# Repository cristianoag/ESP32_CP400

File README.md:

# The Retro Hacker Clone Series: ESP32 CP400

An open hardware and software project to recreate the spirit of the Prologica CP 400, the Brazilian TRS-80 Color Computer 2 compatible home computer, using a modern ESP32-S3 based design.

This design is part of the Retro Hacker ESP32 Clone Series: a planned collection of ESP32-based recreations of classic Brazilian computers from the 1980s. Each machine in the series focuses on keeping the original character and software culture alive while using practical, buildable modern hardware.

The goal is not to build a museum prop. The goal is to make a usable, hackable CP400-inspired machine: real connectors, real keyboard and joystick paths, VGA output, SD-backed storage, and firmware that can run a CoCo 2 / CP400 style environment on inexpensive contemporary hardware.

## Why CP400?

The Prologica CP 400 was one of the memorable Brazilian home computers of the mid-1980s. Built during Brazil's market-reserve era, it was compatible with the Tandy/Radio Shack TRS-80 Color Computer 2, known as the CoCo 2, but arrived with its own Brazilian industrial design, PAL-M video expectations, local peripherals, translated software, and a very particular place in the local 8-bit scene.

Under the hood, the original CP400 family followed the CoCo architecture closely:

- Motorola MC6809E CPU running around 0.895 MHz
- Motorola MC6847 video display generator
- 16 KB or 64 KB RAM configurations
- Extended Color BASIC in ROM
- Cassette, cartridge, joystick, serial, video, and expansion interfaces
- Optional disk support through the CP450 floppy system

This repository explores that machine from both sides: hardware that gives the emulator a dedicated physical home, and software that recreates the CP400/CoCo experience on an ESP32-S3.

## Heritage

<p align="center">
	
	&nbsp;&nbsp;&nbsp;&nbsp;
	
</p>

The ESP32 CP400 sits between two histories: Prologica's Brazilian CP400 family and the Tandy/Radio Shack CoCo 2 platform that inspired it. The project uses those references as historical anchors while building a new, independent ESP32-based recreation.

## Project Goals

- Preserve the CP400/CoCo 2 experience in a form that can be built, studied, and modified.
- Establish the CP400 entry in the broader ESP32 Clone Series for Retro Hacker.
- Use modern parts where they make sense, especially the ESP32-S3 with PSRAM.
- Provide a KiCad hardware design for a CP400-inspired board and peripheral connectors.
- Run an embedded CoCo 2 style emulator with video, USB input, SD storage, virtual disks, and joystick support.
- Keep the design approachable for retrocomputing builders, hardware hackers, and firmware tinkerers.

## Repository Layout

```text
hardware/esp32_clones/         KiCad project for the generic ESP32 clone hardware
hardware/esp32_clones/libraries Project-local KiCad symbols and footprints
software/esp32_cp400_emulator/ PlatformIO firmware for the ESP32-S3 emulator
case/                          Mechanical/case work area
```

## Hardware

The KiCad project lives in `hardware/esp32_clones` and is named `esp32_clones`.

The local KiCad libraries are organized inside:

```text
hardware/esp32_clones/libraries/symbols
hardware/esp32_clones/libraries/footprints
```

The hardware design currently includes project-local footprints and symbols for the ESP32-S3 module, USB connectors, SD card socket, switches, and other board-level parts. The intent is to give the firmware a board that feels more like a small computer than a loose dev kit on a bench.

## Firmware

The firmware lives in `software/esp32_cp400_emulator` and is built with PlatformIO using the Arduino framework for ESP32-S3.

Current software areas include:

- MC6809 emulator core integration
- CoCo 2 / CP400 video mode handling
- VGA output through the ESP32-S3 VGA library
- USB soft-host input support
- SD/MMC storage access
- Virtual floppy disk image handling
- Emulator menu and firmware updater code
- Joystick and keyboard mapping hooks

The PlatformIO environment is configured for an ESP32-S3 DevKitC-style board with 16 MB flash and 8 MB PSRAM:

```ini
[env:esp32-s3-devkitc-1-Modded]
platform = espressif32@6.11.0
board = esp32-s3-devkitc-1-n16r8
framework = arduino
```

The project intentionally pins the Espressif platform version because newer Arduino/ESP32 combinations may change includes and behavior used by the emulator.

### F12 Firmware Update Package

From `software/esp32_cp400_emulator`, generate a firmware package for the F12 update menu with:

```console
make firmware
```

The command builds the configured PlatformIO environment and creates a versioned package such as `dist/ESP32_CP400-1.11.FLH`. Copy that `.FLH` file to the root of the CP400 microSD card, then select **Firmware update** from the F12 menu.

Set the firmware version with `FW_VERSION` near the top of the Makefile, using one major digit and two minor digits. It is compiled into the F12 menu and used in the package filename. A one-off version can be built without editing the file:

```console
make firmware FW_VERSION=1.11
```

The command names can be overridden when needed, for example:

```console
make firmware PIO=platformio PYTHON=py
```

On Windows, the Makefile automatically detects PlatformIO in `%USERPROFILE%/.platformio/penv/Scripts`. Use `make help` to display the detected command.

Firmware release changes are tracked in `software/esp32_cp400_emulator/docs/log.md`.

## Status

This project is under active development. Expect the hardware, pin mapping, emulator behavior, and documentation to evolve together.

Good entry points:

- Open the KiCad project at `hardware/esp32_clones/esp32_clones.kicad_pro`.
- Open the firmware workspace at `software/esp32_cp400_emulator/esp32_cp400_emulator.code-workspace`.
- Review `software/esp32_cp400_emulator/platformio.ini` before building or uploading.

## ROMs and Original Software

Original CP400, CoCo, Extended Color BASIC, Disk BASIC, cartridge, cassette, and floppy software may still be copyrighted. This repository is for original hardware/firmware work and project files. Bring your own legally obtained ROMs and software images when needed.

## Historical Notes

The CP400 was part of a wider Brazilian TRS-Color ecosystem that included machines such as the Codimex CD-6809, LZ Color 64, Dynacom MX-1600, and Varix VC50. The CP400 became the best-known of the Brazilian CoCo-compatible machines, before the home computer market shifted heavily toward MSX and, later, IBM PC compatibles.

That makes it a particularly interesting target for a modern recreation: it sits at the meeting point of Brazilian microcomputer history, Motorola 6809 elegance, CoCo software culture, and the practical charm of 1980s home computing.

## References and Further Reading

- [Prologica CP-400](https://en.wikipedia.org/wiki/Prol%C3%B3gica_CP-400)
- [CP400](https://pt.wikipedia.org/wiki/CP400)
- [TRS-80 Color Computer](https://en.wikipedia.org/wiki/TRS-80_Color_Computer)
- [Prologica](https://pt.wikipedia.org/wiki/Prol%C3%B3gica)
- [Datassette](https://datassette.org/) for Brazilian retrocomputing manuals, magazines, books, and software preservation material

## License

See `LICENSE.txt` for the repository license. The firmware directory also includes its own `license.txt`; check both before reusing or redistributing project materials.

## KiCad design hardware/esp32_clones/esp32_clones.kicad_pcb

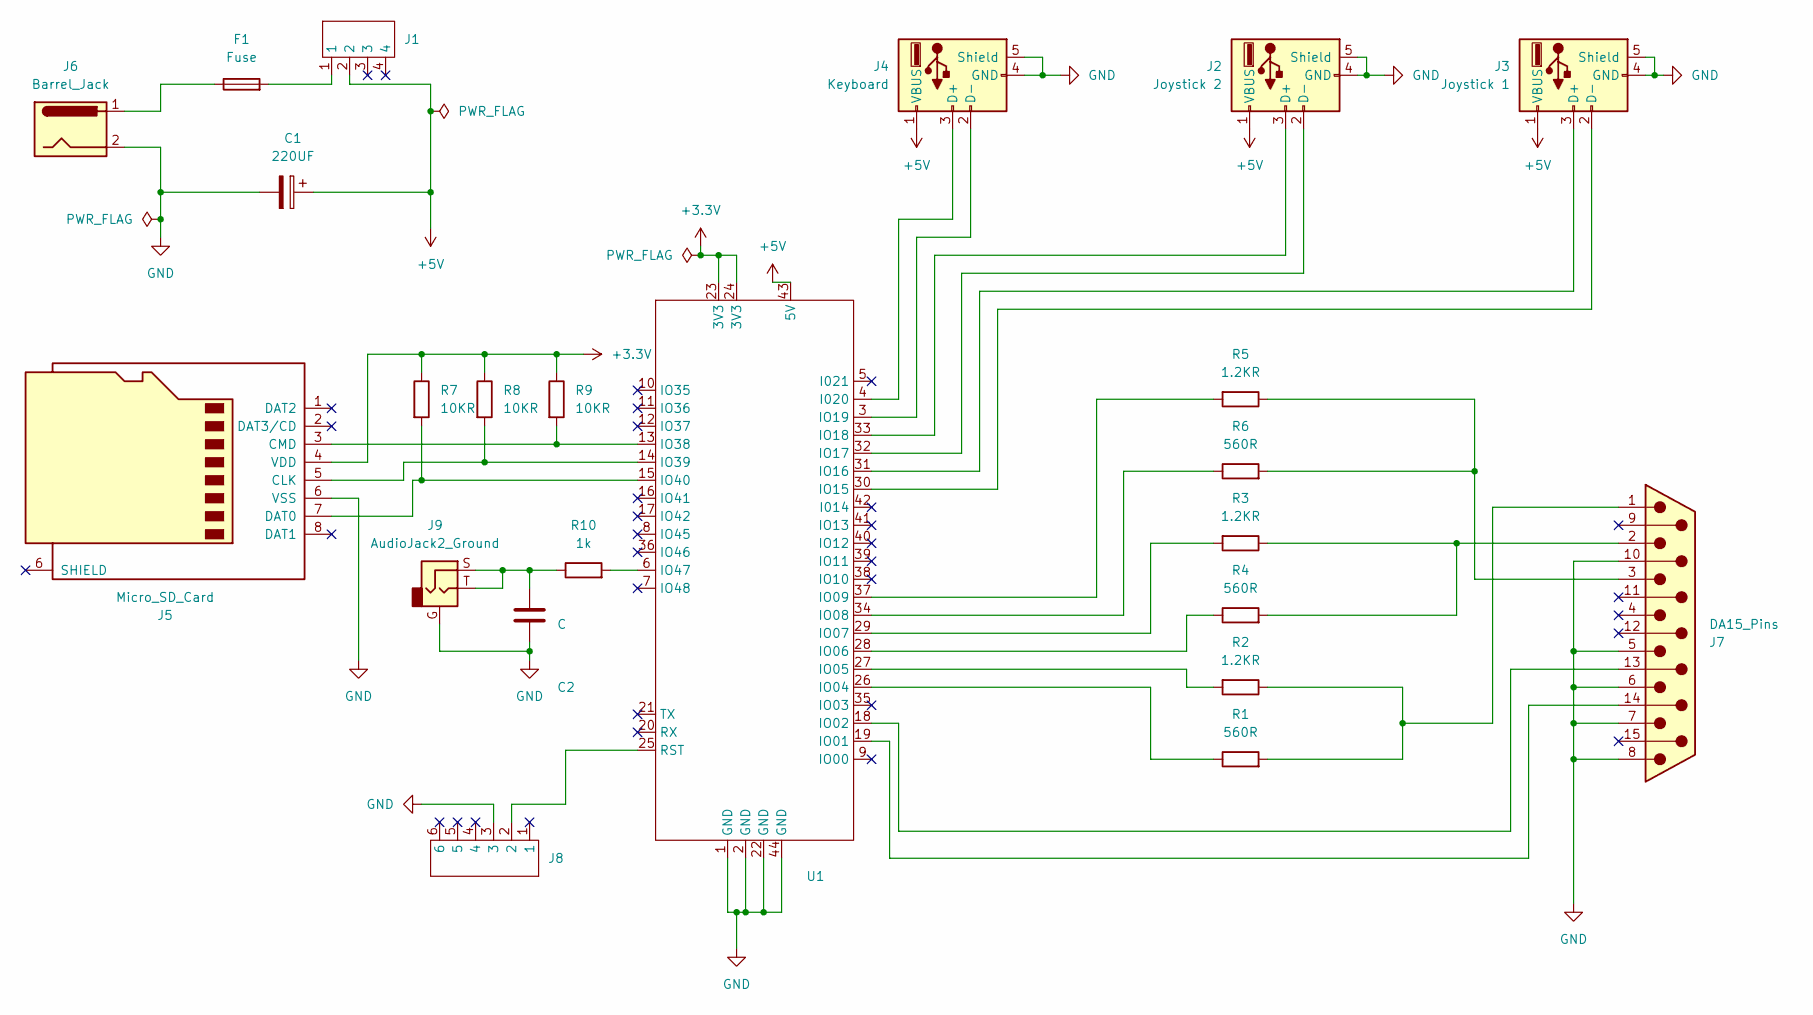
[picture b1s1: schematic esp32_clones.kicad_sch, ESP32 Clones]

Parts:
C1: 220UF; CP_Elec_6.3x3
C2: C; C_0805_2012Metric_Pad1.18x1.45mm_HandSolder
F1: Fuse; Fuse_1210_3225Metric
J1: PS-12E05
J2: Joystick 2; TE_6364372-2
J3: Joystick 1; TE_6364372-2
J4: Keyboard; TE_6364372-2
J5: Micro_SD_Card; Conn_uSDcard
J6: Barrel_Jack; BarrelJack_Horizontal
J7: DA15_Pins; DSUB-15-HD_Socket_Horizontal_P2.29x1.90mm_EdgePinOffset3.03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
J8: PS-22F05
J9: AudioJack2_Ground; PJ-307
R1, R4, R6: 560R; R_0805_2012Metric_Pad1.20x1.40mm_HandSolder
R2, R3, R5: 1.2KR; R_0805_2012Metric_Pad1.20x1.40mm_HandSolder
R7, R8, R9: 10KR; R_0805_2012Metric_Pad1.20x1.40mm_HandSolder
R10: 1k; R_0805_2012Metric_Pad1.20x1.40mm_HandSolder
U1: ESP32-S3-WROOM-1

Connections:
+3.3V: J5.4 (VDD), R7.1, R8.1, R9.1, U1.23 (3V3), U1.24 (3V3)
+5V: C1.1, J1.2, J2.1 (VBUS), J3.1 (VBUS), J4.1 (VBUS), U1.43 (5V)
GND: C1.2, C2.2, J2.4 (GND), J2.5 (Shield), J3.4 (GND), J3.5 (Shield), J4.4 (GND), J4.5 (Shield), J5.6 (VSS), J6.2, J7.5, J7.6, J7.7, J7.8, J7.10, J8.3, J9.G, U1.1 (GND), U1.2 (GND), U1.22 (GND), U1.44 (GND)
unnamed: C2.1, J9.S, J9.T, R10.1
unnamed: F1.1, J6.1
unnamed: F1.2, J1.1
unnamed: J2.3 (D+), U1.33 (IO18)
unnamed: J2.2 (D-), U1.32 (IO17)
unnamed: J3.3 (D+), U1.31 (IO16)
unnamed: J3.2 (D-), U1.30 (IO15)
unnamed: J4.3 (D+), U1.4 (I020)
unnamed: J4.2 (D-), U1.3 (IO19)
unnamed: J5.5 (CLK), R8.2, U1.14 (IO39)
unnamed: J5.3 (CMD), R9.2, U1.13 (IO38)
unnamed: J5.7 (DAT0), R7.2, U1.15 (IO40)
unnamed: J7.13, U1.18 (IO02)
unnamed: J7.14, U1.19 (IO01)
unnamed: J7.1, R1.2, R2.1
unnamed: J7.2, R3.1, R4.2
unnamed: J7.3, R5.1, R6.2
unnamed: R1.1, U1.26 (IO04)
unnamed: R2.2, U1.27 (IO05)
unnamed: R4.1, U1.28 (IO06)
unnamed: R3.2, U1.29 (IO07)
unnamed: R6.1, U1.34 (IO08)
unnamed: R5.2, U1.37 (IO09)
unnamed: R10.2, U1.6 (IO47)
unnamed: J8.2, U1.25 (RST)

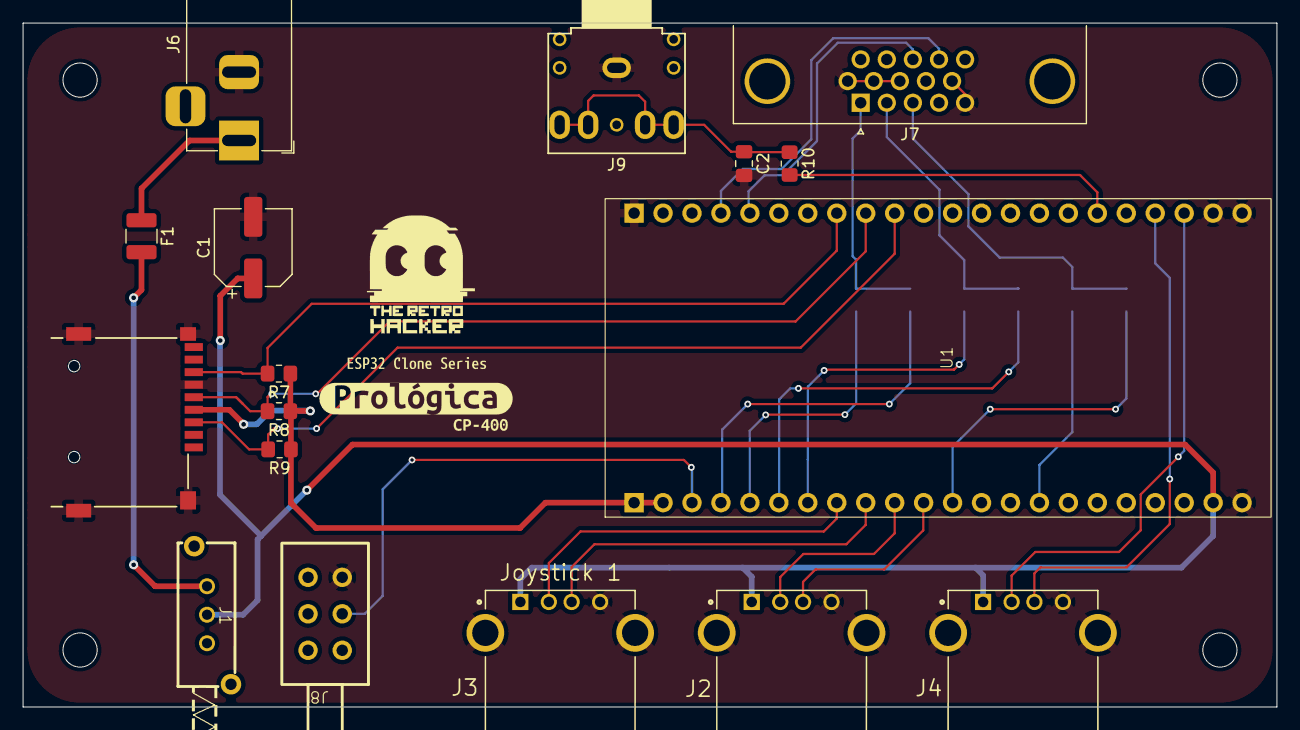
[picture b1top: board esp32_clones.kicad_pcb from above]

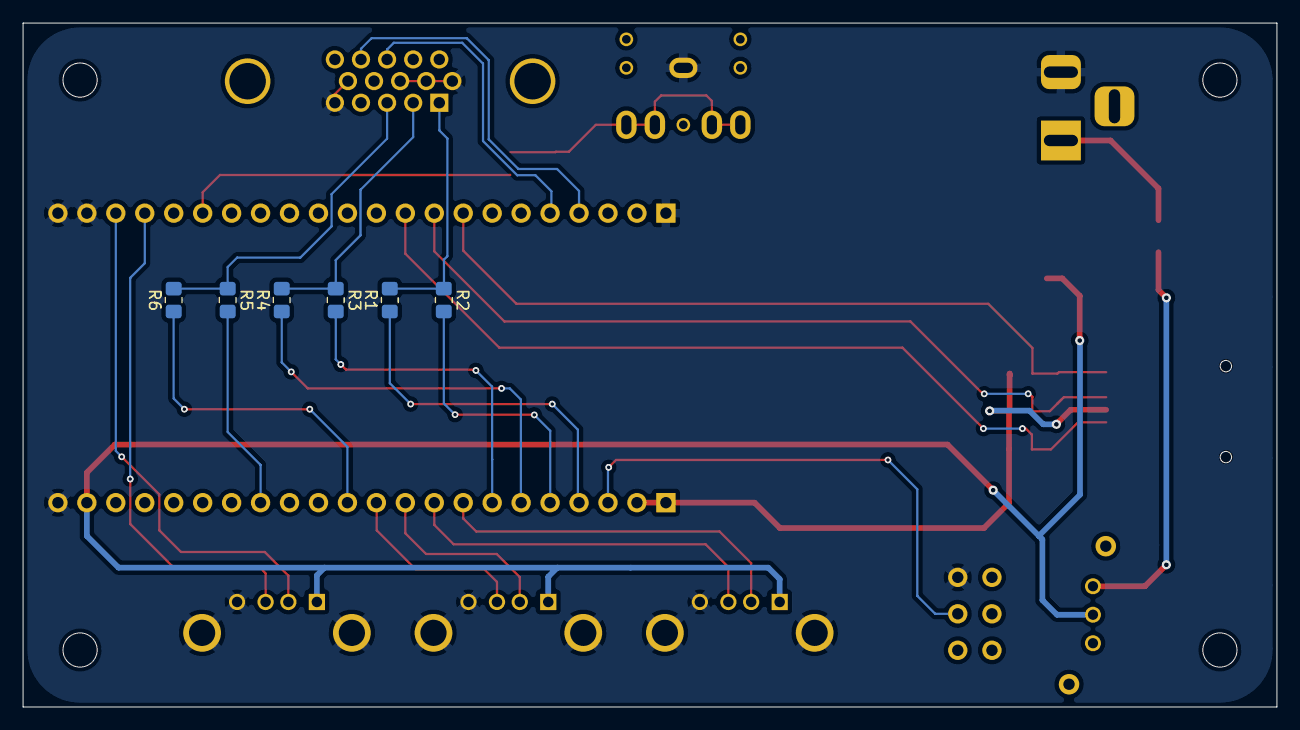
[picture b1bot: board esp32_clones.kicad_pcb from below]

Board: 2 copper layers, 110.0 x 60.0 mm, 26 parts (6 on the bottom side), 28 nets.

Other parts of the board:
kibuzzard-6A32A22E: G***; kibuzzard-6A32A22E
kibuzzard-6A32A25A: G***; kibuzzard-6A32A25A
kibuzzard-6A32A222: G***; kibuzzard-6A32A222

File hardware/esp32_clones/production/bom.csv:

Designator,Footprint,Quantity,Value,LCSC Part #
C1,CP_Elec_6.3x3,1,220UF,
C2,0805,1,C,
F1,1210,1,Fuse,
J1,PS-12E05,1,~,
J2,TE_6364372-2,1,Joystick 2,
J3,TE_6364372-2,1,Joystick 1,
J4,TE_6364372-2,1,Keyboard,
J5,Conn_uSDcard,1,Micro_SD_Card,
J6,BarrelJack_Horizontal,1,Barrel_Jack,
J7,DSUB-15-HD_Socket_Horizontal_P2.29x1.90mm_EdgePinOffset3.03mm_Housed_MountingHolesOffset4.94mm,1,DA15_Pins,
J8,PS-22F05,1,~,
J9,PJ-307,1,AudioJack2_Ground,
"R1, R4, R6",0805,3,560R,
R10,0805,1,1k,
"R2, R3, R5",0805,3,1.2KR,
"R7, R8, R9",0805,3,10KR,
U1,ESP32-S3-WROOM-1,1,~,

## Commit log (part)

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2026-06-17 Add Creative Commons Attribution-NonCommercial-ShareAlike 4.0 International License
2026-06-17 First hardware board
2026-06-17 Remove submodule tracking for .history and add .gitignore
2026-06-17 Add new symbol libraries for ESP32 and power supplies
    - Created a new symbol library for the ESP32 (esp32.kicad_sym) including the esp32-s3-wroom component with detailed pin configurations.
    - Added symbol libraries for PS-12E05 (ps-12e05.kicad_sym) and PS-22F05 (ps-22f05.kicad_sym) with their respective pin definitions.
    - Updated the sym-lib-table to include references to the new libraries for easier access in KiCad.
2026-06-17 Add font data and testing documentation for ESP32 CP400 emulator
    - Introduced a new font file (CoCO2_3_Fonts.txt) containing character data for the emulator.
    - Created a README file in the test directory to outline the purpose of the directory and provide information on unit testing with PlatformIO.
    - Added a ScrapBook.txt file with various BASIC programs and notes related to disk transactions and graphics modes for reference during development.
2026-06-17 Emulation code adjusts
2026-06-17 Add lock files for KiCad project with user information
    - Created lock files for the KiCad PCB, project, and schematic for the ESP32_CP400 hardware.
    - Each lock file contains the hostname and username for the user "Pedro".
2026-06-25 Add footprint for PJ-307 connector
    - Created a new footprint file for the PJ-307 connector in the KiCad format.
    - Included necessary attributes such as reference, value, and layer specifications.
    - Defined pads for through-hole connections with appropriate sizes and drill specifications.
    - Added graphical elements including lines and polygons for silk screen and fabrication layers.
    - Provided a link to the datasheet for reference.

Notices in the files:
hardware/esp32_clones/esp32_clones.kicad_pcb:
This work is licensed under a
